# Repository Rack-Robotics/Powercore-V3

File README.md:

# Powercore V3

A high-efficiency power supply unit designed for Electrical Discharge Machining (EDM) applications.

## Repository Structure

- `circuit-boards/` - KiCAD PCB designs for all modules
- `schematics/` - Schematic PDFs for electronics
- `KiCAD-library/` - Custom component library and 3D models
- `LTSpice/` - Simulation files
- `powercoreV3-firmware/` - Arduino firmware for the RP2040 controller

## Table of Contents

- [PSU HIGHLIGHTS](#psu-highlights)
- [FEATURES](#features)
- [APPLICATIONS](#applications)
- [GENERAL DESCRIPTION](#general-description)
- [SPECIFICATIONS](#specifications)
- [Recommended Operating Conditions](#recommended-operating-conditions)
- [DEVICE INTERFACES](#device-interfaces)
  - [Power Input Connector](#power-input-connector)
  - [Power Output Connector](#power-output-connector)
  - [Digital Interface Connector](#digital-interface-connector)
  - [USB-Micro Serial Interface](#usb-micro-serial-interface)
- [THEORY OF OPERATION](#theory-of-operation)
- [OPERATION MODES](#operation-modes)
  - [Startup Behavior](#startup-behavior)
  - [Idle Mode](#idle-mode)
  - [Iso-Frequency Mode](#iso-frequency-mode)
  - [Edge-Detection Mode](#edge-detection-mode)
- [APPLICATION EXAMPLE: MINIMUM IMPLEMENTATION](#application-example-minimum-implementation)
- [EMC & EMI](#emc--emi)
- [Images of PCBA](#images-of-pcba)
- [Typical PSU Waveforms](#typical-psu-waveforms)
- [LICENSE](#license)
- [⚠️ HIGH VOLTAGE SAFETY WARNING ⚠️](#️-high-voltage-safety-warning-️)

## PSU HIGHLIGHTS

1. Optimized for wire EDM applications
2. Maximum input power: 300W with high efficiency topology
3. Adjustable output parameters:
   - Machining Duty Cycle: 1% to 10%
   - Spark Initiation Voltage: 64V to 100V
   - Machining Frequency: 5kHz to 10kHz
4. USB serial interface for configuration and telemetry
5. PWM feedback output for external feedrate control
6. Edge detection capability for workpiece probing

## FEATURES

- **Dual-Converter Topology** with resonant converter and boost converter for high-efficiency EDM machining
- Input power optimized for desktop/micro-scale wire EDM (300W maximum, 48V input)
- Output parameters configurable via USB-micro serial interface
- Integrated protection features: pulse-skipping, overcurrent protection, and inrush protection
- Open-source electronics, firmware, and CAD files

## APPLICATIONS

- Wire EDM
- Plunge EDM
- Desktop-scale EDM machines
- Portable and battery-powered EDM machines
- Scientific research and development

## GENERAL DESCRIPTION

The Powercore V3 provides precision control of machining parameters including duty cycle, spark initiation voltage, and machining frequency. The system is optimized for desktop-scale wire EDM applications. The open-source design enables customization for research, development, and specialized EDM implementations.

## SPECIFICATIONS

| SPECIFICATION | Min | Max Value | UNIT |
| --- | --- | --- | --- |
| Average Input Power | 10 | 300 | W |
| Input Voltage | 47.8 | 48.2 | V |
| Input Current | 0.625 | 6.25 | A |
| Machining Duty Cycle | 1 | 10 | % |
| Spark Initiation Voltage | 64 | 100 | V |
| Machining Frequency | 5,000 | 10,000 | Hz |
| Machining Current (1) | 40 | 70 | A |
| PWM Feedback Duty Cycle | 0 | 100 | % |
| PWM Feedback Voltage | 0 | 3.3 | V |
| PWM Feedback Frequency  | — | 1,000 | Hz |
| PWM Feedback Output Impedance | 1,010 | 9,990 | Ω |
| Enable Input Voltage | 3.0 | 3.5 | V |
| Enable Input Impedance | 1,010 | 9,990 | Ω |

(1) Machining current depends on output cable impedance and discharge characteristics. Not regulated by constant-current control. Lower-impedance output cables provide higher machining current.

## Recommended Operating Conditions

| Parameter | Value |
| --- | --- |
| Ambient Temperature | 0°C to 30°C |
| Ingress Protection Rating | IP20 (Indoor use) |
| Relative Humidity | 20% to 80% (non-condensing) |
| Input Cable Gauge | 16 AWG minimum |
| Output Cable Gauge | 16 AWG stranded, 300V rated |
| Output Cable Length | <1 meter, twisted pair |
| Cooling | Forced air cooling recommended |

## DEVICE INTERFACES

### POWER INPUT CONNECTOR

Input power connects via 2-position lever-action Wago connector accepting 16 AWG conductors. 48VDC input must be connected before applying 5V via USB-micro. If USB power is applied before 48VDC input, the microcontroller enters fault mode.

### POWER OUTPUT CONNECTOR 

Output connects via 2-position lever-action Wago connector accepting 16 AWG stranded conductors. Output cable must be twisted pair, <1 meter length, and either shielded/grounded or contained within a shielded/grounded enclosure.

### DIGITAL INTERFACE CONNECTOR 

4-position JST-XH header provides communication with external controllers. Exposes 3.3V and GND from RP2040 microcontroller with current-limiting resistors.

- **Enable Input**: Output is enabled when this input is connected to 3.3V or external 3.3V supply with common ground. 10kΩ pull-down resistor to GND.
- **Feedback Output**: Reports EDM power consumption via active-low PWM signal. 100% duty cycle indicates no power consumption from machining; 0% indicates short circuit. Maintain 10-90% duty cycle during machining by adjusting feedrate. 10kΩ pull-down resistor to GND. External low-pass filter can convert to analog feedback.

### USB-MICRO SERIAL INTERFACE

Exposes USB-micro connector of RP2040 Pico module for parameter configuration and telemetry. Default baud rate: 115,200.

**Warning**: Device requires both 48VDC input power AND 5V USB power. 48VDC must be connected first, or device enters fault mode.

| SERIAL COMMAND | DESCRIPTION |
| --- | --- |
| SEND_TELEMETRY | Request device status and parameters |
| SET_ALL_PARAMETERS | Configure machining parameters: discharges, duty cycle, frequency, initiation voltage<br>Format: 'SET_ALL_PARAMETERS [discharges] [duty_cycle] [frequency] [voltage]'<br>Example: 'SET_ALL_PARAMETERS 0 0.10 5000 100' |
| EDM_ISOFREQUENCY_MODE | Enter EDM iso-frequency mode |
| EDGE_DETECTION_MODE | Enter edge detection mode |
| RESET_DEVICE | Reset device |

Invalid commands return list of valid commands.

## THEORY OF OPERATION

The Powercore V3 generates controlled electrical discharges for EDM machining. The system cycles through spark initiation, current delivery, and discharge termination at high frequency (5-20kHz).

**Spark Initiation Voltage**: Determines spark formation conditions. Higher voltages create longer, more intense discharges suitable for harder materials.

**Machining Duty Cycle**: Controls discharge duration. Longer duty cycles increase material removal rate but may increase surface roughness.

**Machining Frequency**: Sets discharge repetition rate. Lower frequencies can increase material removal rate but may reduce surface finish quality.

**Machining Current**: Ranges from 40A to 70A, determined by fixed 48VDC output during current phase and combined impedance of output cables and discharge gap. Current is not user-adjustable.

## OPERATION MODES

### STARTUP BEHAVIOR 

On power-up, output is disabled (high-impedance state). Power management module initializes and pi-filter capacitors charge to 48V with inrush protection. Brief audible noise (~1 second) is normal during startup. Output current sensor calibrates and serial communication establishes.

**BOOST CONVERTER SELF-TEST**: System tests boost converter module and I2C digital potentiometer. If I2C communication fails, device reports 'ERROR: DPOT is not at expected position'. 

During startup, digital potentiometer cycles through settings 0-110, generating boost converter output voltage lookup table (50V-160V). If voltage range is insufficient, device enters fault mode and reports 'ERROR: DPOT voltage range is less than expected'.

Normal startup sequence via serial:
```
Setting DPOT to minimum position...
Waiting for voltage to stabilize...
Reading voltages for DPOT lookup table...
Boost Converter Digital Potentiometer Voltage Table:
0: 51
1: 52
...
109: 161
110: 166
```

Successful startup indicated by solid green LED and "Setup complete" message. Device enters IDLE mode.

### IDLE MODE

Output remains in high-impedance state until enable input is asserted (3.3V). No discharges occur in idle mode.

### ISO-FREQUENCY MODE

Fixed-frequency discharge mode. Default mode or activated via 'EDM_ISOFREQUENCY_MODE' command. Enable input must be asserted (3.3V) to begin operation.

**ISO-FREQUENCY MODE PARAMETERS**

| PARAMETER | Min | Default | Max | Unit |
| --- | --- | --- | --- | --- |
| Machining Duty Cycle | 1 | 10 | 10 | % |
| Machining Frequency | 5,000 | 1,000 | 10,000 | Hz |
| Spark Initiation Voltage | 64 | 80 | 100 | V |

### EDGE-DETECTION MODE

Probe mode for detecting electrode-workpiece contact via PWM feedback. Intended for setup and calibration only, not for machining. Activated via 'EDGE_DETECTION_MODE' command with enable input asserted.

## APPLICATION EXAMPLE: MINIMUM IMPLEMENTATION

Minimum system configuration:

| Connection | Requirements |
| --- | --- |
| Power Input | 48V, 300W supply via 16 AWG stranded wire |
| USB-Micro | 5V supply or PC connection. **Note**: 48V must be connected first |
| Enable Input | Connect to 3.3V after power supplies are connected |
| Power Output | Positive (+) to workpiece, negative (-) to electrode (wire/tool) |

## EMC & EMI

The Powercore V3 power supply unit is housed in a precision-machined, billet-aluminum enclosure, fully grounded to minimize electromagnetic interference. When no output cables are connected, radiated emissions are negligible. However, when output cables are attached, radiated emissions vary based on cable characteristics, including length, twist, and wire gauge.

**Requirements**: Output cables must be shielded, grounded, and twisted. Poor cable design may increase emissions and interfere with sensitive equipment.

**Installation**: Complete machining setup should be enclosed, shielded, and grounded. EMC compliance is installer's responsibility.

## Images of PCBA

### PCBA View 1

### PCBA View 2

### PCBA View 3

### PCBA View 4

## Typical PSU Waveforms

### Output Stage Switch Control
Normal behavior of output stage switches during EDM iso-frequency mode. The enable (yellow trace) and high-current phase (red trace) switches are both active at the same time, permitting current flow from the positive electrode to the negative electrode. The high-voltage switch is active several microseconds before each switching event, for the purpose of charging the output capacitor to the spark initiation voltage (blue trace).

### Gap Voltage with Electrodes Separated
Normal behavior of output stages during EDM iso-frequency mode, with the electrodes separated by several millimeters under distilled water. The positive (+) electrode (red trace) shows the change in gap voltage when the output capacitor is charged and then slowly discharged through the water.

### EDM Discharge Behavior
Normal behavior of output stages during EDM iso-frequency mode, during electrical discharge machining. The positive (+) electrode voltage changes rapidly during an EDM discharge; transitioning from the spark initiation voltage (here 80V) to the gap machining voltage (~40V) in several hundred nanoseconds.

### Boost Converter Operation
Normal behavior of the boost converter module. The MOSFET gate (blue trace) presents with short pulses, which are used to maintain a stable output voltage. The output voltage will be set by the I2C digital potentiometer to between 64 and 150 V.

Startup behavior of device. Two seconds are required for inrush protection and serial communication initiation. Subsequently, the boost converter and output voltage sensor collaborate to create the lookup table for the I2C digital potentiometer. Once the lookup table is constructed, the boost converter is set to its default 80V setting.

## LICENSE 
The Powercore V3 2025 by Rack Robotics, Inc. is licensed under the Creative Commons Attribution-NonCommercial-ShareAlike 4.0 International License (CC BY-NC-SA 4.0).

### You are free to:
- **Share** — copy and redistribute the material in any medium or format
- **Adapt** — remix, transform, and build upon the material

### Under the following terms:
- **Attribution** — You must give appropriate credit, provide a link to the license, and indicate if changes were made
- **NonCommercial** — You may not use the material for commercial purposes
- **ShareAlike** — If you remix, transform, or build upon the material, you must distribute your contributions under the same license as the original
- **No additional restrictions** — You may not apply legal terms or technological measures that legally restrict others from doing anything the license permits

### Notices:
You do not have to comply with the license for elements of the material in the public domain or where your use is permitted by an applicable exception or limitation.

No warranties are given. The license may not give you all of the permissions necessary for your intended use. For example, other rights such as publicity, privacy, or moral rights may limit how you use the material.

For the full license text, see: https://creativecommons.org/licenses/by-nc-sa/4.0/

This includes all hardware designs, firmware, documentation, and associated files in this repository. Commercial use requires explicit written permission from the project maintainers. 

### Trademark
The name 'Powercore' and 'Rack Robotics' are property of Rack Robotics, Inc. and are only to be used by Rack Robotics, Inc. Any derivative works must remove both marks unless written permission to use either or both marks is provided by Rack Robotics, Inc.

## ⚠️ HIGH VOLTAGE SAFETY WARNING ⚠️

**DANGER - HIGH VOLTAGE PRESENT**
This device generates and outputs high-voltage DC, which could be hazardous. Before operating, building, or servicing this equipment, read and understand all safety warnings.

ELECTRICAL HAZARDS
- **DANGEROUS VOLTAGES PRESENT**: Output voltages up to 150V DC can cause electrical shock or burns
- **STORED ENERGY**: Internal capacitors retain dangerous voltages even when power is disconnected
- **DISCHARGES**: High-energy discharges can cause burns, eye damage, and ignite flammable materials

LEGAL DISCLAIMER
- Users assume all responsibility for safe operation and compliance with local electrical codes
- This equipment is intended for use by qualified professionals only
- Improper use may result in serious injury, death, or property damage
- The manufacturer disclaims all liability for injuries or damages resulting from improper use
**IF YOU ARE NOT QUALIFIED TO WORK WITH HIGH-VOLTAGE EQUIPMENT, DO NOT PROCEED**

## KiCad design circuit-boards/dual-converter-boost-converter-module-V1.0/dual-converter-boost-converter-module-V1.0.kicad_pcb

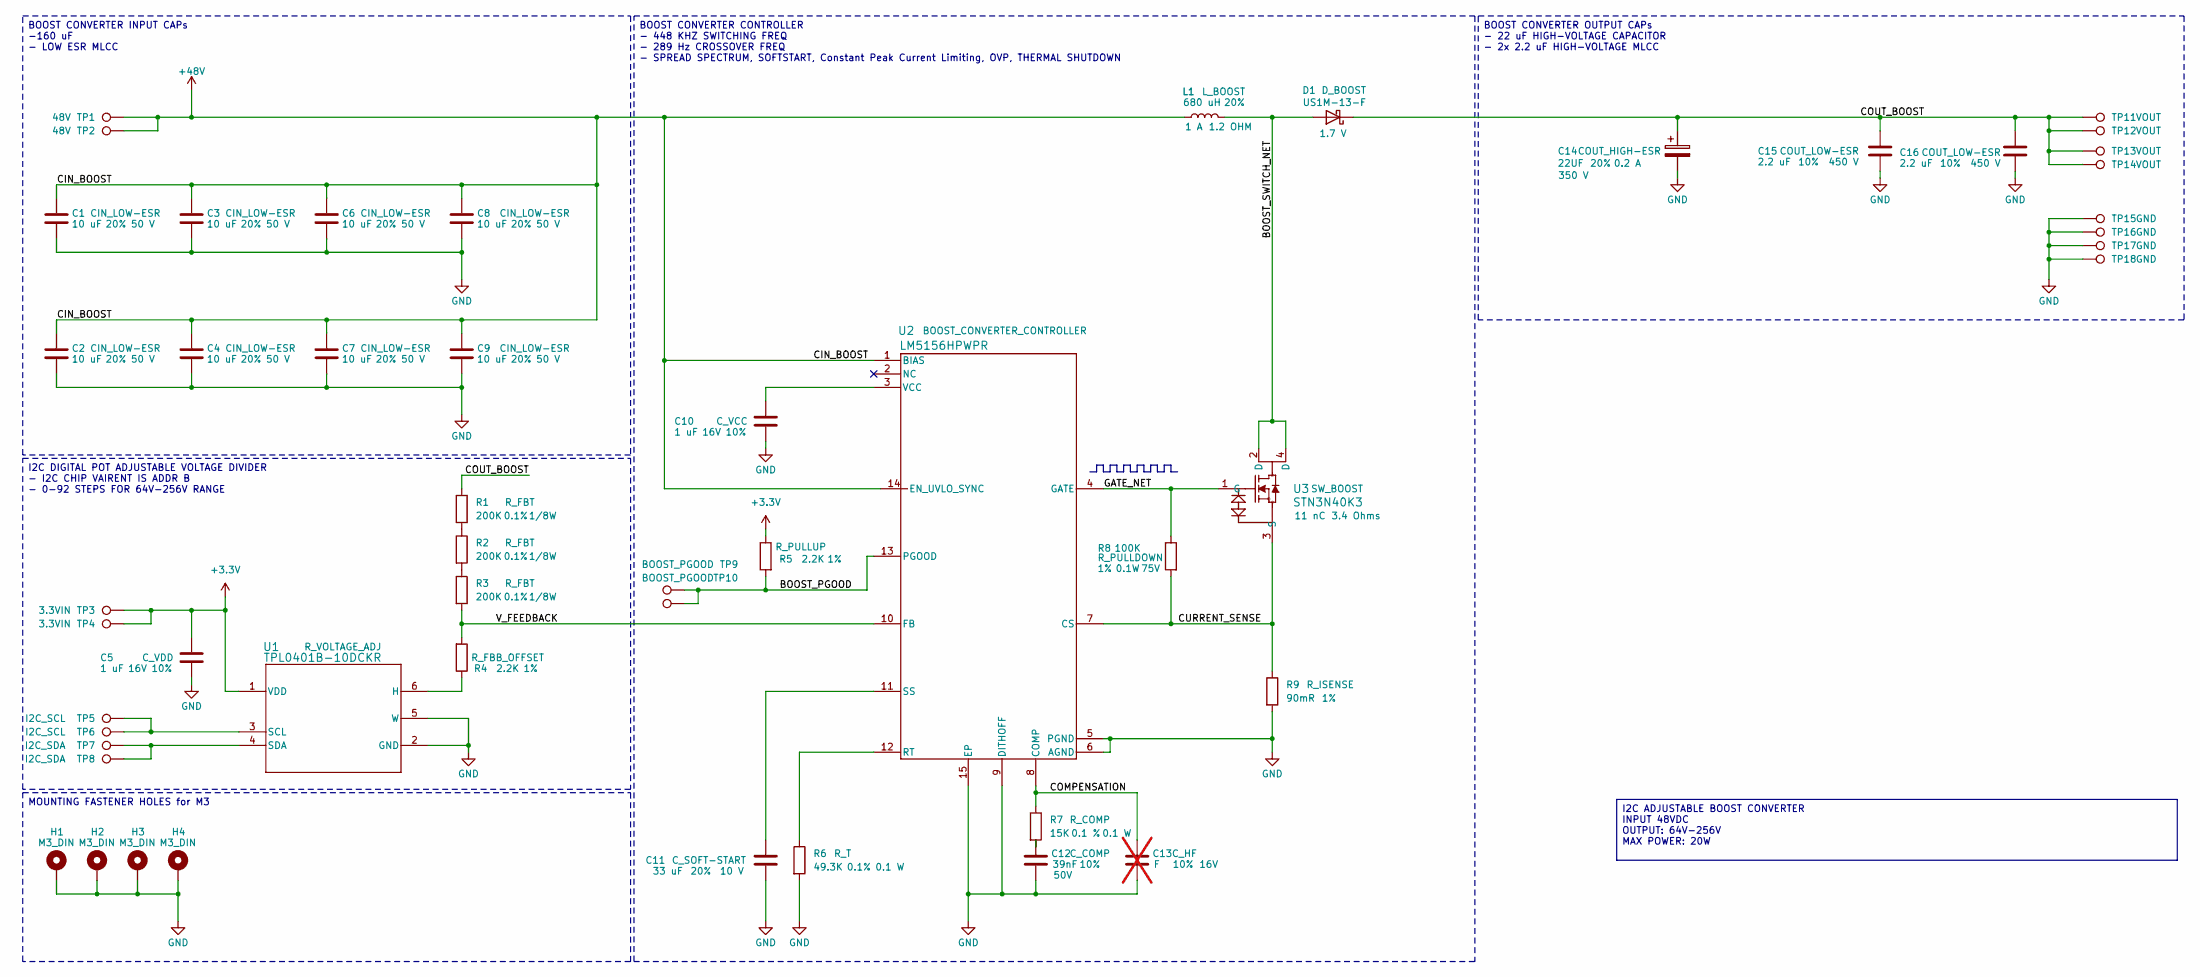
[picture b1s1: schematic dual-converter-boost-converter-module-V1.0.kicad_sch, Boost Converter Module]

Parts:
C1, C2, C3, C4, C6, C7, C8, C9: 10 uF; C_1206_3216Metric; Tolerance 20%; Max Voltage 50 V; Manufacturer# CL31A106MBHNNNE; LCSC Part # C96600
C5, C10: 1 uF; C_0603_1608Metric; Tolerance 10%; Max Voltage 16V; Manufacturer# CC0603KRX5R7BB105; LCSC Part # C106215
C11: 33 uF; C_0805_2012Metric; Tolerance 20%; Max Voltage 10 V; Manufacturer# C2012X5R1A336MTJ00E; LCSC Part # C342635
C12: 39nF; C_0603_1608Metric; Tolerance 10%; Max Voltage 50V; Manufacturer# CC0603KRX7R9BB393; LCSC Part # C107091
C13: F; C_0603_1608Metric; Tolerance 10%; Max Voltage 16V; Manufacturer# NULL; LCSC Part # NULL; not fitted
C14: 22UF; 226TTA350M; Tolerance 20%; Max Voltage 350 V; Manufacturer# 226TTA350M; LCSC Part # C6077372
C15, C16: 2.2 uF; C_2220_5750Metric; Tolerance 10%; Max Voltage 450 V; Manufacturer# TDK Corporation; LCSC Part # C445674
D1: US1M-13-F; D_SMA; Forward Voltage 1.7 V; Manufacturer# US1M-13-F; LCSC Part # C99333
H1, H2, H3, H4: M3_DIN; MountingHole_3.2mm_M3_DIN965_Pad_TopBottom; Manufacturer# NULL
L1: 680 uH; SRR1210-681M; Tolerance 20%; Manufacturer# SRR1210-681M; LCSC Part # NULL
R1, R2, R3: 200K; R_0805_2012Metric; Tolerance 0.1%; Manufacturer# RT0805BRD07200KL; LCSC Part # C728645
R4, R5: 2.2K; R_0603_1608Metric; Tolerance 1%; Manufacturer# 13-RC0603FR-132K2LCT-ND; LCSC Part # C3032396
R6: 49.3K; R_0603_1608Metric; Tolerance 0.1%; Manufacturer# AT0603BRD0749K3L; LCSC Part # C861433
R7: 15K; R_0603_1608Metric; Tolerance 0.1 %; Manufacturer# AT0603BRD0715KL; LCSC Part # C855633
R8: 100K; R_0603_1608Metric; Tolerance 1%; Max Voltage 75V; Manufacturer# CRCW0603100KFKEA; LCSC Part # C844916
R9: 90mR; R_1206_3216Metric; Tolerance 1%; Manufacturer# RL1206FR-070R09L; LCSC Part # C375525
TP1, TP2: 48V; TestPoint_TestPoint_Pad_2.0x2.0mm_No_Silkscreen; Manufacturer# NULL
TP3, TP4: 3.3VIN; TestPoint_TestPoint_Pad_2.0x2.0mm_No_Silkscreen; Manufacturer# NULL
TP5, TP6: I2C_SCL; TestPoint_TestPoint_Pad_2.0x2.0mm_No_Silkscreen; Manufacturer# NULL
TP7, TP8: I2C_SDA; TestPoint_TestPoint_Pad_2.0x2.0mm_No_Silkscreen; Manufacturer# NULL
TP9, TP10: BOOST_PGOOD; TestPoint_TestPoint_Pad_2.0x2.0mm_No_Silkscreen; Manufacturer# NULL
TP11, TP12, TP13, TP14: VOUT; TestPoint_TestPoint_Pad_2.0x2.0mm_No_Silkscreen; Manufacturer# NULL
TP15, TP16, TP17, TP18: GND; TestPoint_TestPoint_Pad_2.0x2.0mm_No_Silkscreen; Manufacturer# NULL
U1: TPL0401B-10DCKR; Manufacturer# TPL0401B-10DCKR; LCSC Part # C2666599
U2: LM5156HPWPR; lm5156h; Manufacturer# LM5156HPWPR; LCSC Part # C2867852
U3: STN3N40K3; Manufacturer# STN3N40K3; LCSC Part # C128261

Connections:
+3.3V: C5.1, R5.1, TP3.1, TP4.1, U1.1 (VDD)
+48V: C1.1, C2.1, C3.1, C4.1, C6.1, C7.1, C8.1, C9.1, L1.1, TP1.1, TP2.1, U2.1 (BIAS), U2.14 (EN_UVLO_SYNC)
/BOOST_PGOOD: R5.2, TP9.1, TP10.1, U2.13 (PGOOD)
/BOOST_SWITCH_NET: D1.2 (A), L1.2, U3.2 (D), U3.4 (D)
/COMPENSATION: C13.1, R7.1, U2.8 (COMP)
/COUT_BOOST: C14.1, C15.1, C16.1, D1.1 (K), R1.1, TP11.1, TP12.1, TP13.1, TP14.1
/CURRENT_SENSE: R8.2, R9.1, U2.7 (CS), U3.3 (S)
/GATE_NET: R8.1, U2.4 (GATE), U3.1 (G)
/V_FEEDBACK: R3.2, R4.2, U2.10 (FB)
GND: C1.2, C2.2, C3.2, C4.2, C5.2, C6.2, C7.2, C8.2, C9.2, C10.2, C11.2, C12.2, C13.2, C14.2, C15.2, C16.2, H1.1, H2.1, H3.1, H4.1, R6.2, R9.2, TP15.1, TP16.1, TP17.1, TP18.1, U1.2 (GND), U1.5 (W), U2.5 (PGND), U2.6 (AGND), U2.9 (DITHOFF), U2.15 (EP)
unnamed: C12.1, R7.2
unnamed: R1.2, R2.1
unnamed: R2.2, R3.1
unnamed: R4.1, U1.6 (H)
unnamed: TP5.1, TP6.1, U1.3 (SCL)
unnamed: TP7.1, TP8.1, U1.4 (SDA)
unnamed: R6.1, U2.12 (RT)
unnamed: C11.1, U2.11 (SS)
unnamed: C10.1, U2.3 (VCC)

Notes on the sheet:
BOOST CONVERTER CONTROLLER - 448 KHZ SWITCHING FREQ - 289 Hz CROSSOVER FREQ - SPREAD SPECTRUM, SOFTSTART, Constant Peak Current Limiting, OVP, THERMAL SHUTDOWN
BOOST CONVERTER INPUT CAPs -160 uF - LOW ESR MLCC
I2C DIGITAL POT ADJUSTABLE VOLTAGE DIVIDER - I2C CHIP VAIRENT IS ADDR B - 0-92 STEPS FOR 64V-256V RANGE
MOUNTING FASTENER HOLES for M3
BOOST CONVERTER OUTPUT CAPs - 22 uF HIGH-VOLTAGE CAPACITOR - 2x 2.2 uF HIGH-VOLTAGE MLCC
I2C ADJUSTABLE BOOST CONVERTER INPUT 48VDC OUTPUT: 64V-256V MAX POWER: 20W

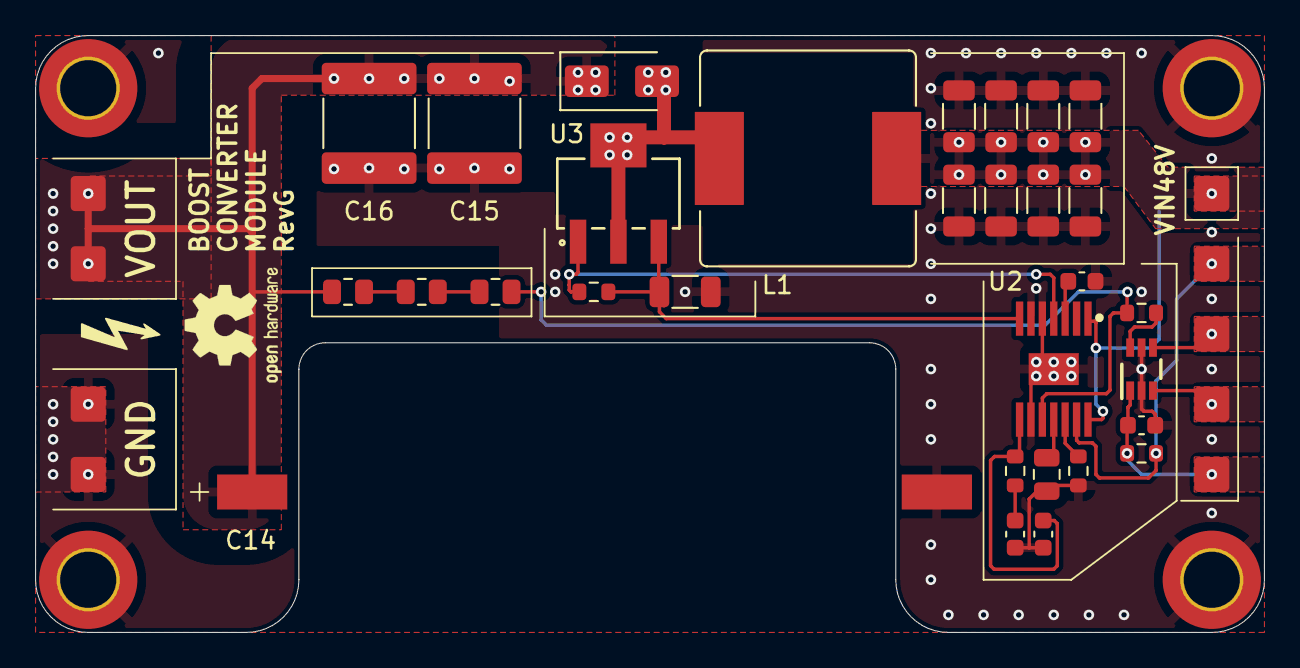
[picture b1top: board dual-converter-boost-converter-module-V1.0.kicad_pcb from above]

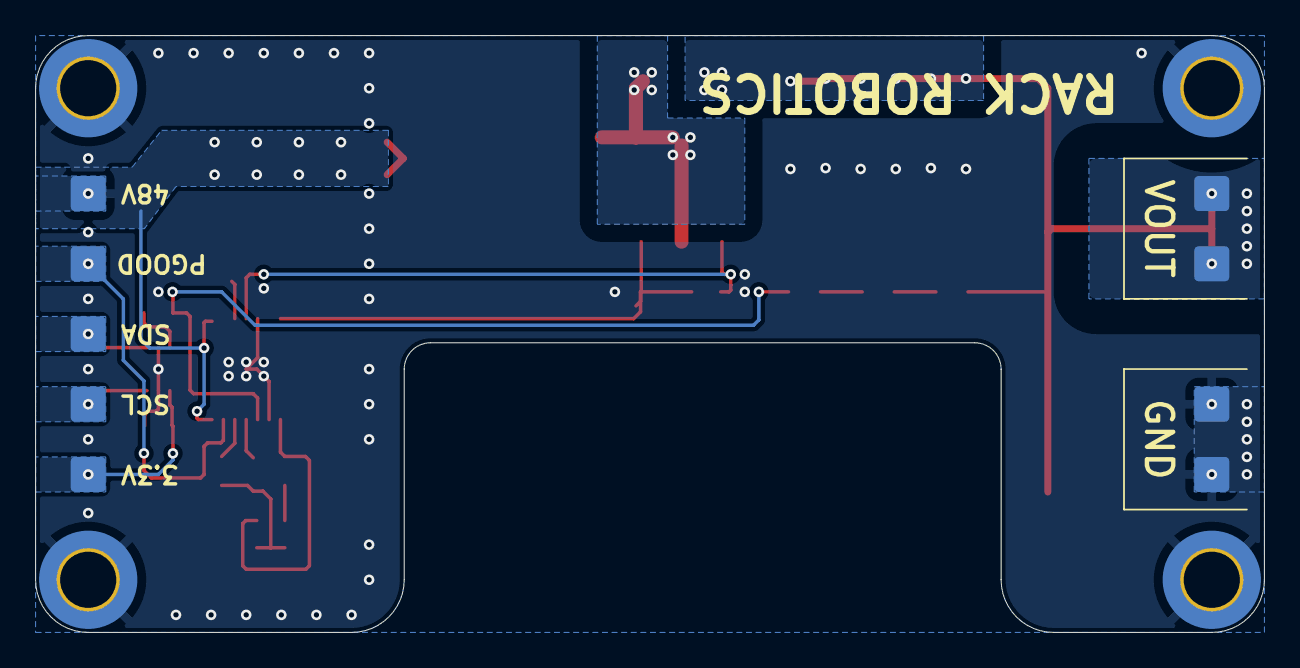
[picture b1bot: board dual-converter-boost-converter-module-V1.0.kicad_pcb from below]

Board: 4 copper layers, 70.0 x 34.0 mm, 52 parts (9 on the bottom side), 19 nets.

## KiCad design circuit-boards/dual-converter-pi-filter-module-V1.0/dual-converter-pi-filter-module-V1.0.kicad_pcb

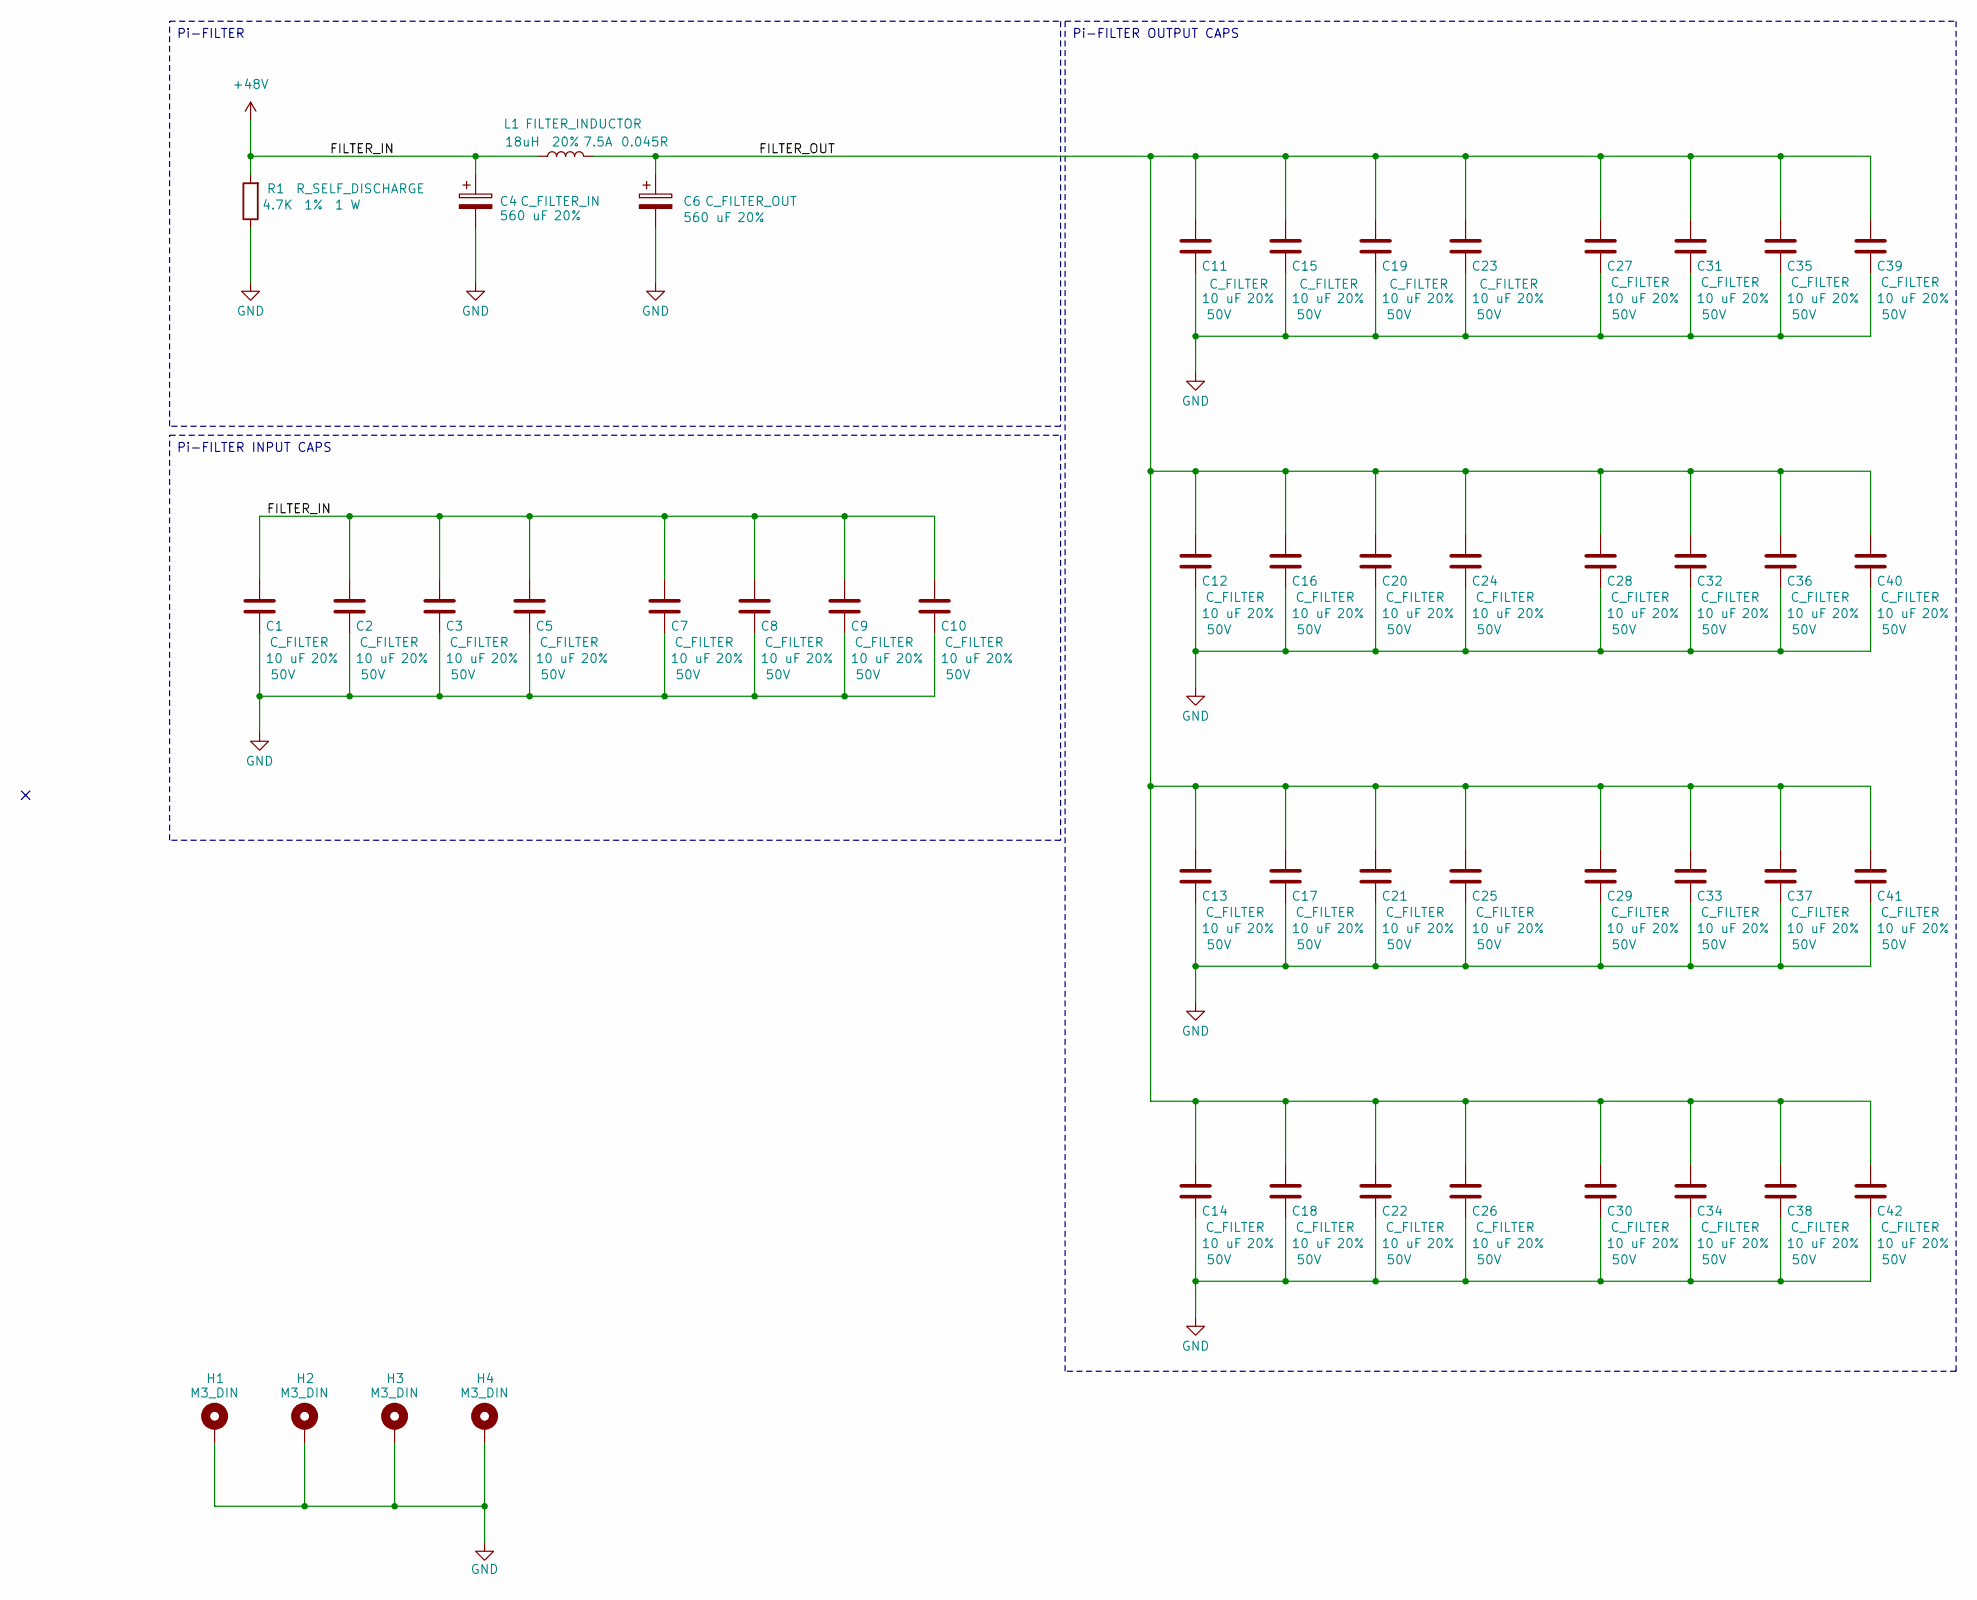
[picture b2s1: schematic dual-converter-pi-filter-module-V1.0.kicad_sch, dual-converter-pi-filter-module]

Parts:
C1, C2, C3, C5, C7, C8, C9, C10, C11, C12, C13, C14, C15, C16, C17, C18, C19, C20, C21, C22, C23, C24, C25, C26, C27, C28, C29, C30, C31, C32, C33, C34, C35, C36, C37, C38, C39, C40, C41, C42: 10 uF; C_1206_3216Metric; Tolerance 20%; Max Voltage 50V; Manufacturer# CL31A106MBHNNNE; LCSC Part # C96600
C4, C6: 560 uF; PHA225; Tolerance 20%; Manufacturer# PHA225MLP3560QE4; LCSC Part # C3274794
H1, H2, H3, H4: M3_DIN; MountingHole_3.2mm_M3_DIN965_Pad_TopBottom; Manufacturer# NULL
L1: 18uH; SRP1245A; Tolerance 20%; Current Rating 7.5A; Manufacturer# SRP1245A-180M; LCSC Part # C5926042
R1: 4.7K; R_2512_6332Metric; Tolerance 1%; Manufacturer# RC2512JK-074K7L; LCSC Part # C878291

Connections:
+48V: C1.1, C2.1, C3.1, C4.1, C5.1, C7.1, C8.1, C9.1, C10.1, L1.1, R1.2
/FILTER_OUT: C6.1, C11.1, C12.1, C13.1, C14.1, C15.1, C16.1, C17.1, C18.1, C19.1, C20.1, C21.1, C22.1, C23.1, C24.1, C25.1, C26.1, C27.1, C28.1, C29.1, C30.1, C31.1, C32.1, C33.1, C34.1, C35.1, C36.1, C37.1, C38.1, C39.1, C40.1, C41.1, C42.1, L1.2
GND: C1.2, C2.2, C3.2, C4.2, C5.2, C6.2, C7.2, C8.2, C9.2, C10.2, C11.2, C12.2, C13.2, C14.2, C15.2, C16.2, C17.2, C18.2, C19.2, C20.2, C21.2, C22.2, C23.2, C24.2, C25.2, C26.2, C27.2, C28.2, C29.2, C30.2, C31.2, C32.2, C33.2, C34.2, C35.2, C36.2, C37.2, C38.2, C39.2, C40.2, C41.2, C42.2, H1.1, H2.1, H3.1, H4.1, R1.1

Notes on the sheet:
Pi-FILTER INPUT CAPS
Pi-FILTER
Pi-FILTER OUTPUT CAPS

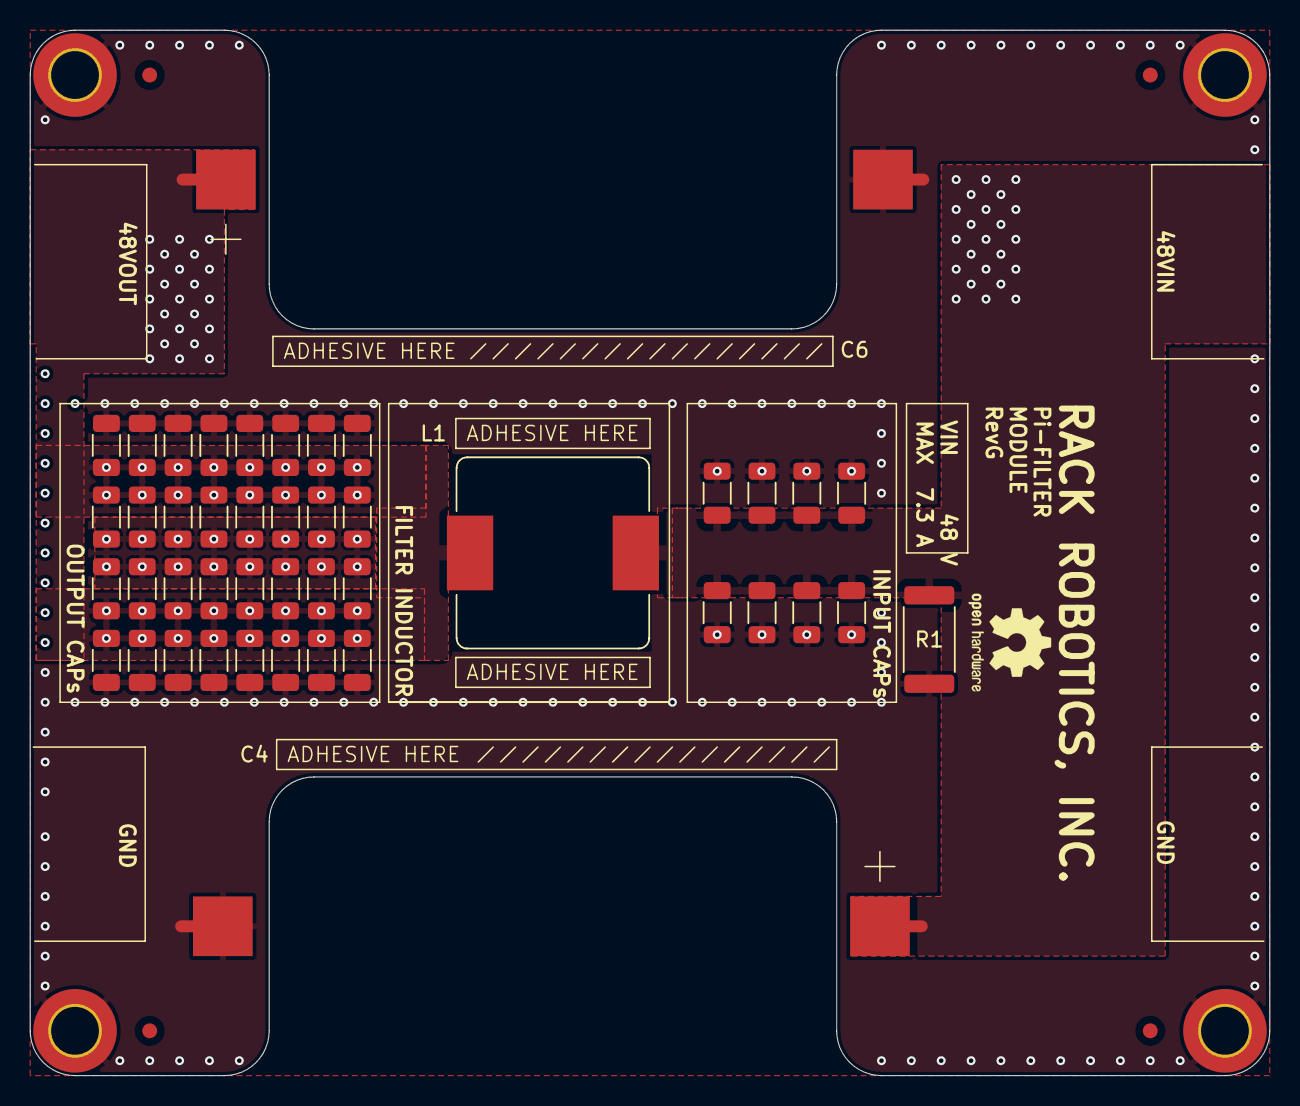
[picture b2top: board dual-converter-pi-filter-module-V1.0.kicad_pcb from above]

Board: 4 copper layers, 83.0 x 70.0 mm, 48 parts (0 on the bottom side), 3 nets.

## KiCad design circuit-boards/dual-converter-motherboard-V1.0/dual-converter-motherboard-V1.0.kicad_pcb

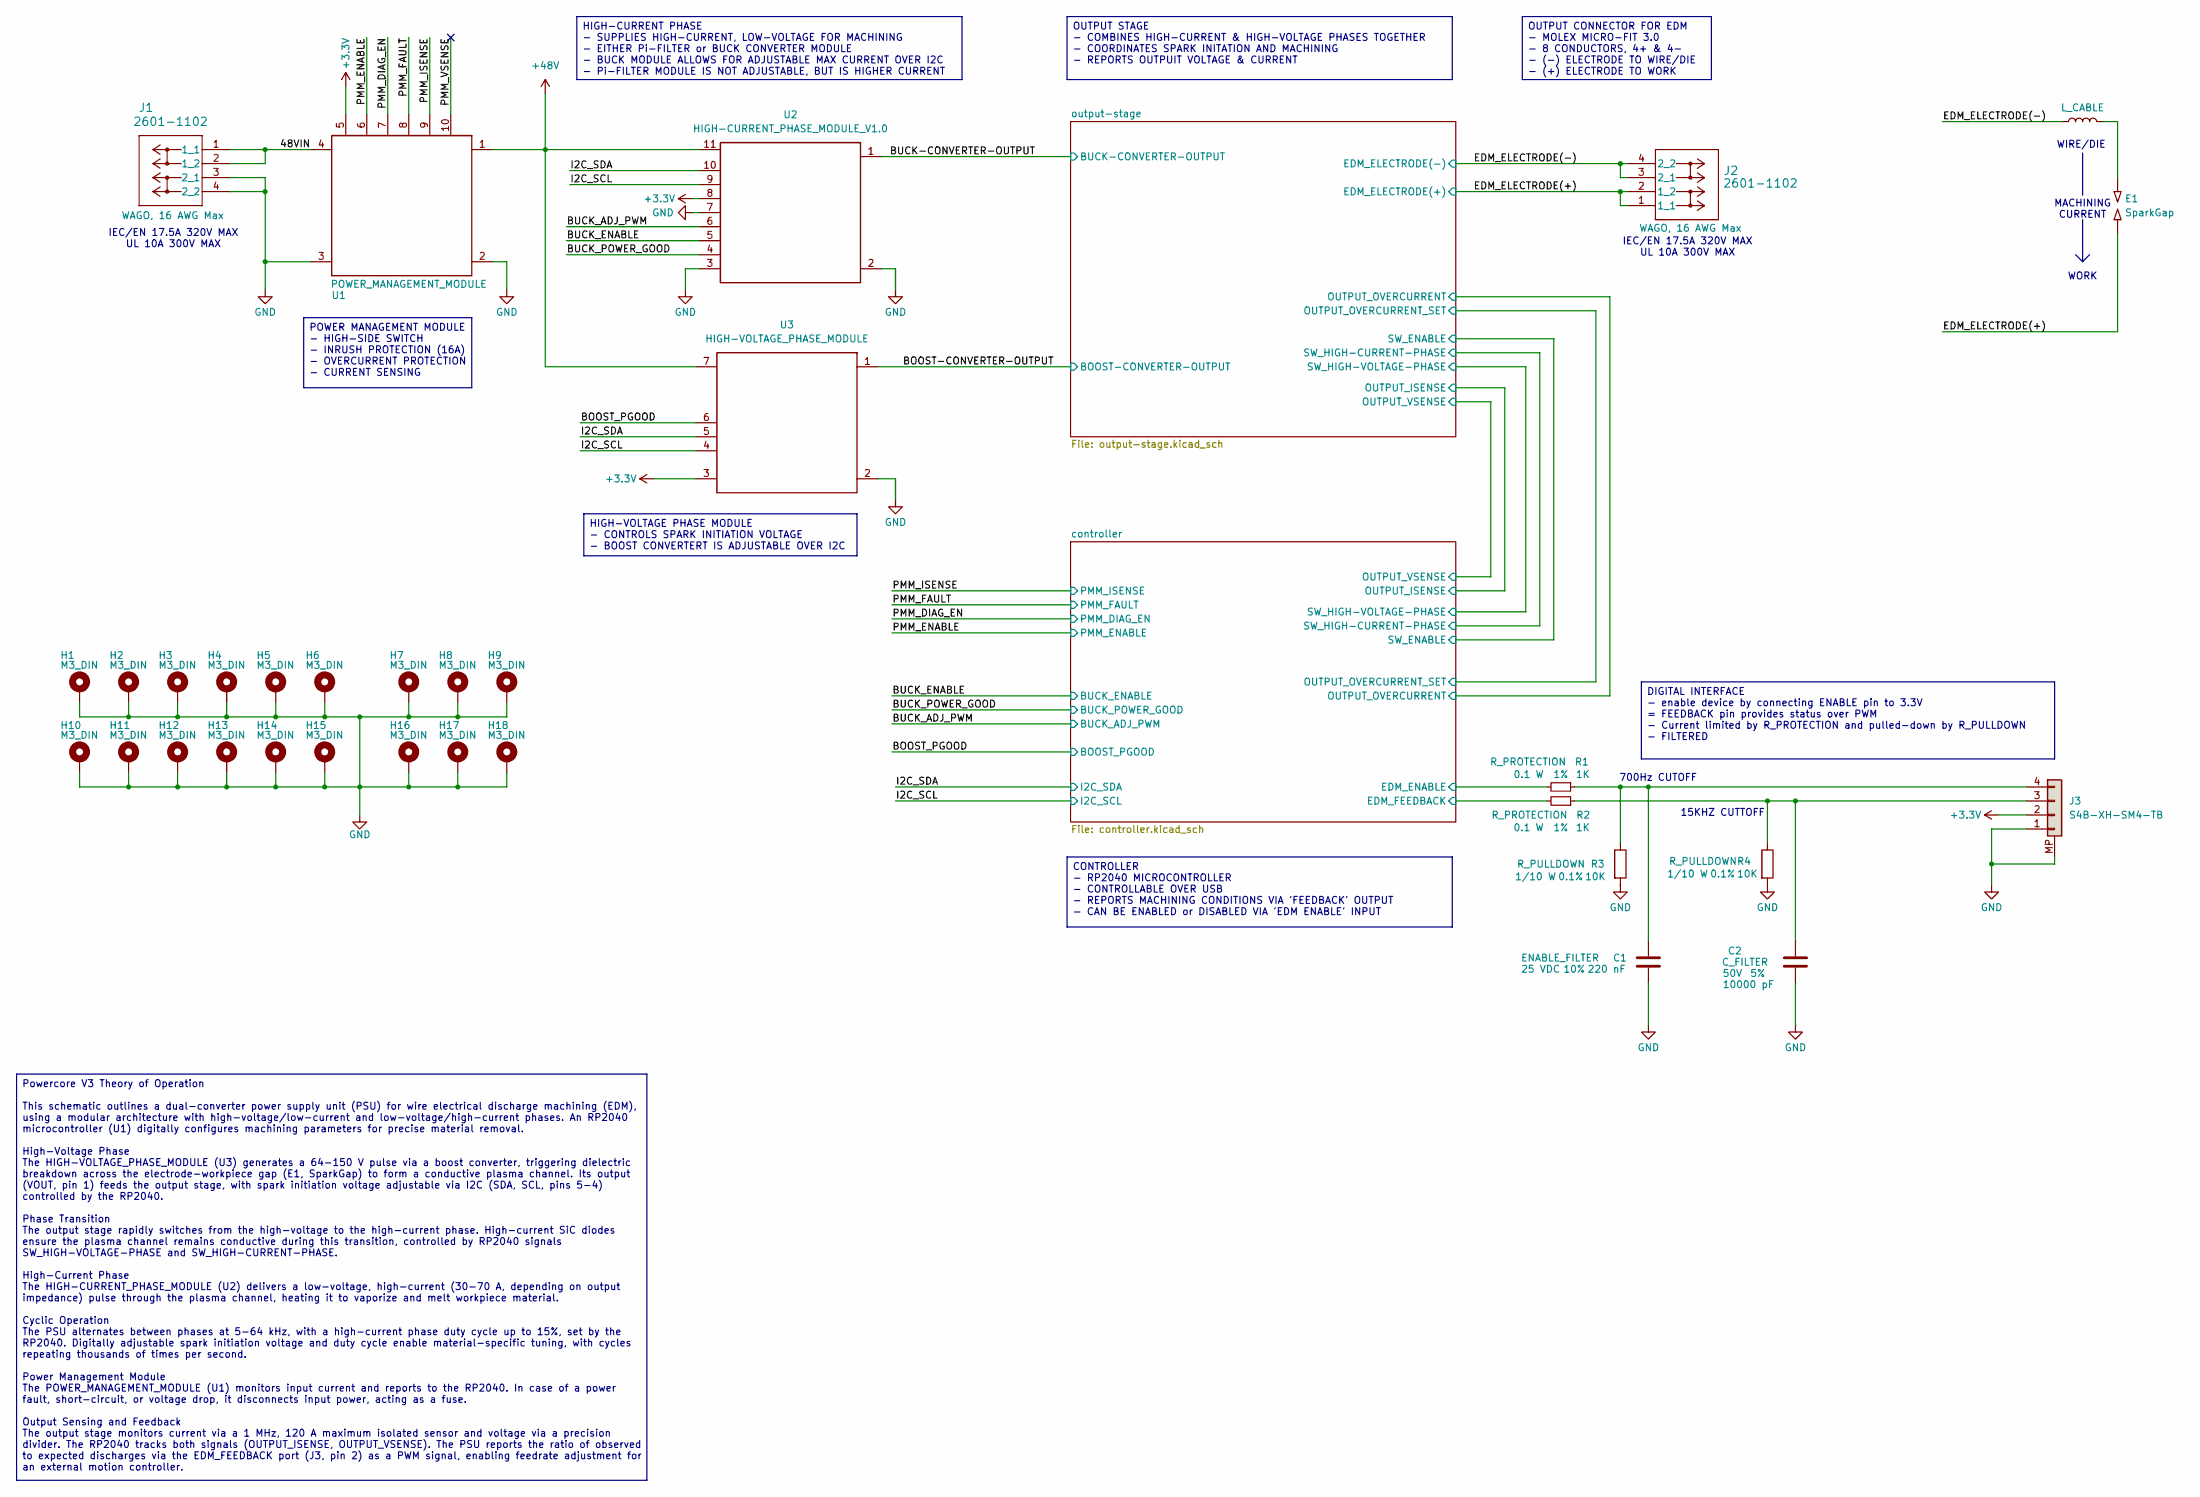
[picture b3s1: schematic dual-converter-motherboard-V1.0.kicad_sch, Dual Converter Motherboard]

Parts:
C1: 220 nF; C_0603_1608Metric; Tolerance 10%; Max Voltage 25 VDC; Manufacturer# AC0603KRX7R9BB224; LCSC Part # C726565
C2: 10000 pF; C_0603_1608Metric; Tolerance 5%; Max Voltage 50V; Manufacturer# CC0603JRX7R9BB103; LCSC Part # C115056
E1: SparkGap; NULL; Manufacturer# NULL; LCSC Part # NULL
H1, H2, H3, H4, H5, H6, H7, H8, H9, H10, H11, H12, H13, H14, H15, H16, H17, H18: M3_DIN; MountingHole_3.2mm_M3_DIN965_Pad_TopBottom; Manufacturer# NULL
J1, J2: 2601-1102; Manufacturer# 2601-1102; LCSC Part # C7509568
J3: S4B-XH-SM4-TB; Manufacturer# S4B-XH-SM4-TB; LCSC Part # C161861
L_CABLE1: L_CABLE
R1, R2: 1K; R_0603_1608Metric; Tolerance 1%; Manufacturer# RC0603FR-071KL; LCSC Part # C22548
R3, R4: 10K; R_0603_1608Metric; Tolerance 0.1%; Manufacturer# RC0603BR-0710KL; LCSC Part # C20161635
U1: POWER_MANAGEMENT_MODULE; POWER_MANAGEMENT_MODULE_FOOTPRINT_V1.0
U2: HIGH-CURRENT_PHASE_MODULE_V1.0; HIGH-CURRENT_PHASE_MODULE_FOOTPRINT_V1.0
U3: HIGH-VOLTAGE_PHASE_MODULE; HIGH-VOLTAGE_PHASE_MODULE_FOOTPRINT_V1.0

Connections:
+3.3V: J3.2, U1.5, U2.8 (3.3VIN), U3.3 (GND); also elsewhere on the board
+48V: U1.1 (VOUT), U2.11 (48VIN), U3.7 (48VIN); also elsewhere on the board
/48VIN: J1.1 (1_1), J1.2 (1_2), U1.4 (VIN)
/BOOST-CONVERTER-OUTPUT: U3.1 (VOUT); also elsewhere on the board
/BOOST_PGOOD: U3.6 (PGOOD); also elsewhere on the board
/BUCK-CONVERTER-OUTPUT: U2.1 (VOUT); also elsewhere on the board
/BUCK_ADJ_PWM: U2.6 (PWM_ADJ); also elsewhere on the board
/BUCK_ENABLE: U2.5 (ENABLE); also elsewhere on the board
/BUCK_POWER_GOOD: U2.4 (PGOOD); also elsewhere on the board
/EDM_ELECTRODE(+): E1.1, J2.1 (1_1), J2.2 (1_2); also elsewhere on the board
/EDM_ELECTRODE(-): J2.3 (2_1), J2.4 (2_2), L_CABLE1.1; also elsewhere on the board
/I2C_SCL: U2.9 (SCL), U3.4 (SCL); also elsewhere on the board
/I2C_SDA: U2.10 (SDA), U3.5 (SDA); also elsewhere on the board
/PMM_DIAG_EN: U1.7; also elsewhere on the board
/PMM_ENABLE: U1.6; also elsewhere on the board
/PMM_FAULT: U1.8; also elsewhere on the board
/PMM_ISENSE: U1.9; also elsewhere on the board
/PMM_VSENSE: U1.10
/PMM_VSENSE_1: U1.10
/controller/EDM_ENABLE: R1.2; also elsewhere on the board
/controller/EDM_FEEDBACK: R2.2; also elsewhere on the board
GND: C1.2, C2.2, H1.1, H2.1, H3.1, H4.1, H5.1, H6.1, H7.1, H8.1, H9.1, H10.1, H11.1, H12.1, H13.1, H14.1, H15.1, H16.1, H17.1, H18.1, J1.3 (2_1), J1.4 (2_2), J3.1, J3.MP, R3.2, R4.2, U1.2, U1.3, U2.2 (GND), U2.3 (GND), U2.7 (GND), U3.2 (GND); also elsewhere on the board
unnamed: E1.2, L_CABLE1.2
unnamed: C2.1, J3.3, R2.1, R4.1
unnamed: C1.1, J3.4, R1.1, R3.1

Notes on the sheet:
IEC/EN 17.5A 320V MAX UL 10A 300V MAX
WORK
700Hz CUTOFF
MACHINING CURRENT
WIRE/DIE
15KHZ CUTTOFF
CONTROLLER - RP2040 MICROCONTROLLER - CONTROLLABLE OVER USB - REPORTS MACHINING CONDITIONS VIA 'FEEDBACK' OUTPUT - CAN BE ENABLED or DISABLED VIA 'EDM ENABLE' INPUT
HIGH-VOLTAGE PHASE MODULE - CONTROLS SPARK INITIATION VOLTAGE - BOOST CONVERTERT IS ADJUSTABLE OVER I2C
OUTPUT CONNECTOR FOR EDM - MOLEX MICRO-FIT 3.0 - 8 CONDUCTORS, 4+ & 4- - (-) ELECTRODE TO WIRE/DIE - (+) ELECTRODE TO WORK
HIGH-CURRENT PHASE - SUPPLIES HIGH-CURRENT, LOW-VOLTAGE FOR MACHINING - EITHER Pi-FILTER or BUCK CONVERTER MODULE - BUCK MODULE ALLOWS FOR ADJUSTABLE MAX CURRENT OVER I2C - Pi-FILTER MODULE IS NOT ADJUSTABLE, BUT IS HIGHER CURRENT
Powercore V3 Theory of Operation This schematic outlines a dual-converter power supply unit (PSU) for wire electrical discharge machining (EDM), using a modular architecture with high-voltage/low-current and low-voltage/high-current phases. An RP2040 microcontroller (U1) digitally configures machin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
OUTPUT STAGE - COMBINES HIGH-CURRENT & HIGH-VOLTAGE PHASES TOGETHER - COORDINATES SPARK INITATION AND MACHINING - REPORTS OUTPUIT VOLTAGE & CURRENT
POWER MANAGEMENT MODULE - HIGH-SIDE SWITCH - INRUSH PROTECTION (16A) - OVERCURRENT PROTECTION - CURRENT SENSING
DIGITAL INTERFACE - enable device by connecting ENABLE pin to 3.3V = FEEDBACK pin provides status over PWM - Current limited by R_PROTECTION and pulled-down by R_PULLDOWN - FILTERED
